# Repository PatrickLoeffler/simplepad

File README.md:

# Simplepad

A simple programmable 3x3 macropad with a rotary encoder.

## Features
- PCB designed to be easy to etch (wide traces etc.) manually without special tools.
- Intentionally simple: 9 Cherry MX switches and a rotary encoder, no LEDs, displays etc.

## Cloning
Use ```git clone --recursive https://github.com/frederik-h/simplepad.git```
to clone this repository with its git submodules (KiCad part libraries).

## Making changes
The PCB was made using [KiCad](https://kicad-pcb.org/) version 5.0.2.

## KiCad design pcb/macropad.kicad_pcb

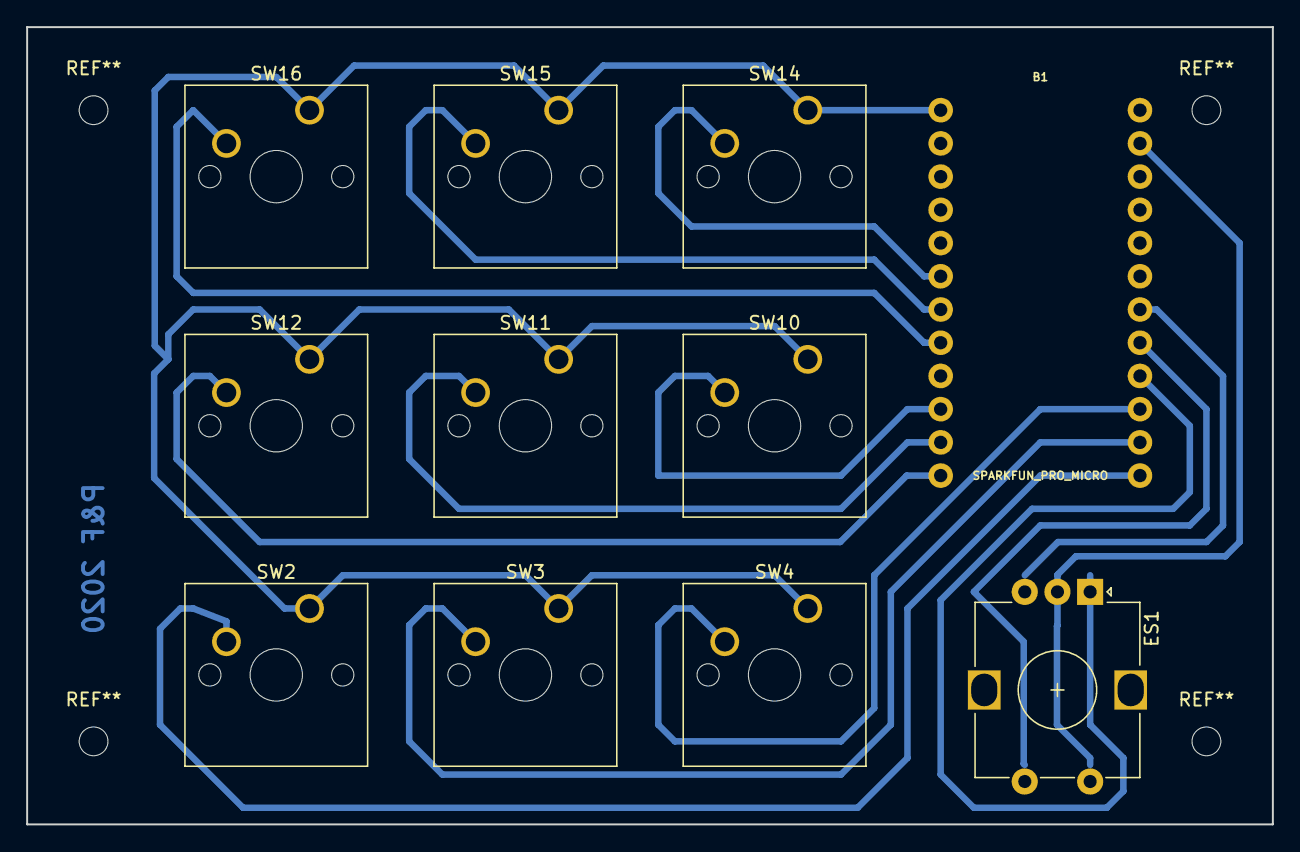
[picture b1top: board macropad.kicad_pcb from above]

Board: 2 copper layers, 95.2 x 61.0 mm, 11 parts (0 on the bottom side), 14 nets.

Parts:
B1: SPARKFUN_PRO_MICRO
ES1: ENCODER-SWITCH; RotaryEncoder_Alps_EC12E-Switch_Vertical_H20mm
SW2, SW3, SW4, SW10, SW11, SW12, SW14, SW15, SW16: SW_SPST; SW_Cherry_MX1A_1.00u_PCB

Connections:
unnamed: B1.1, SW2.1, SW3.1, SW4.1, SW10.1, SW11.1, SW12.1, SW14.1, SW15.1, SW16.1
unnamed: B1.6, SW14.2
unnamed: B1.7, SW15.2
unnamed: B1.8, SW16.2
unnamed: B1.10, SW10.2
unnamed: B1.11, SW11.2
unnamed: B1.12, SW12.2
unnamed: B1.13, SW2.2
unnamed: B1.14, SW3.2
unnamed: B1.15, SW4.2
unnamed: B1.16, ES1.A
unnamed: B1.17, ES1.SW+
unnamed: B1.18, ES1.B
unnamed: B1.23, ES1.C, ES1.SW-

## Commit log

2020-06-25 Add PCB files
    * Add KiCad files for Simplepad PCB
    * Update LICENSE and README.md

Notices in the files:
README.md:
License: CC BY-SA 4.0
